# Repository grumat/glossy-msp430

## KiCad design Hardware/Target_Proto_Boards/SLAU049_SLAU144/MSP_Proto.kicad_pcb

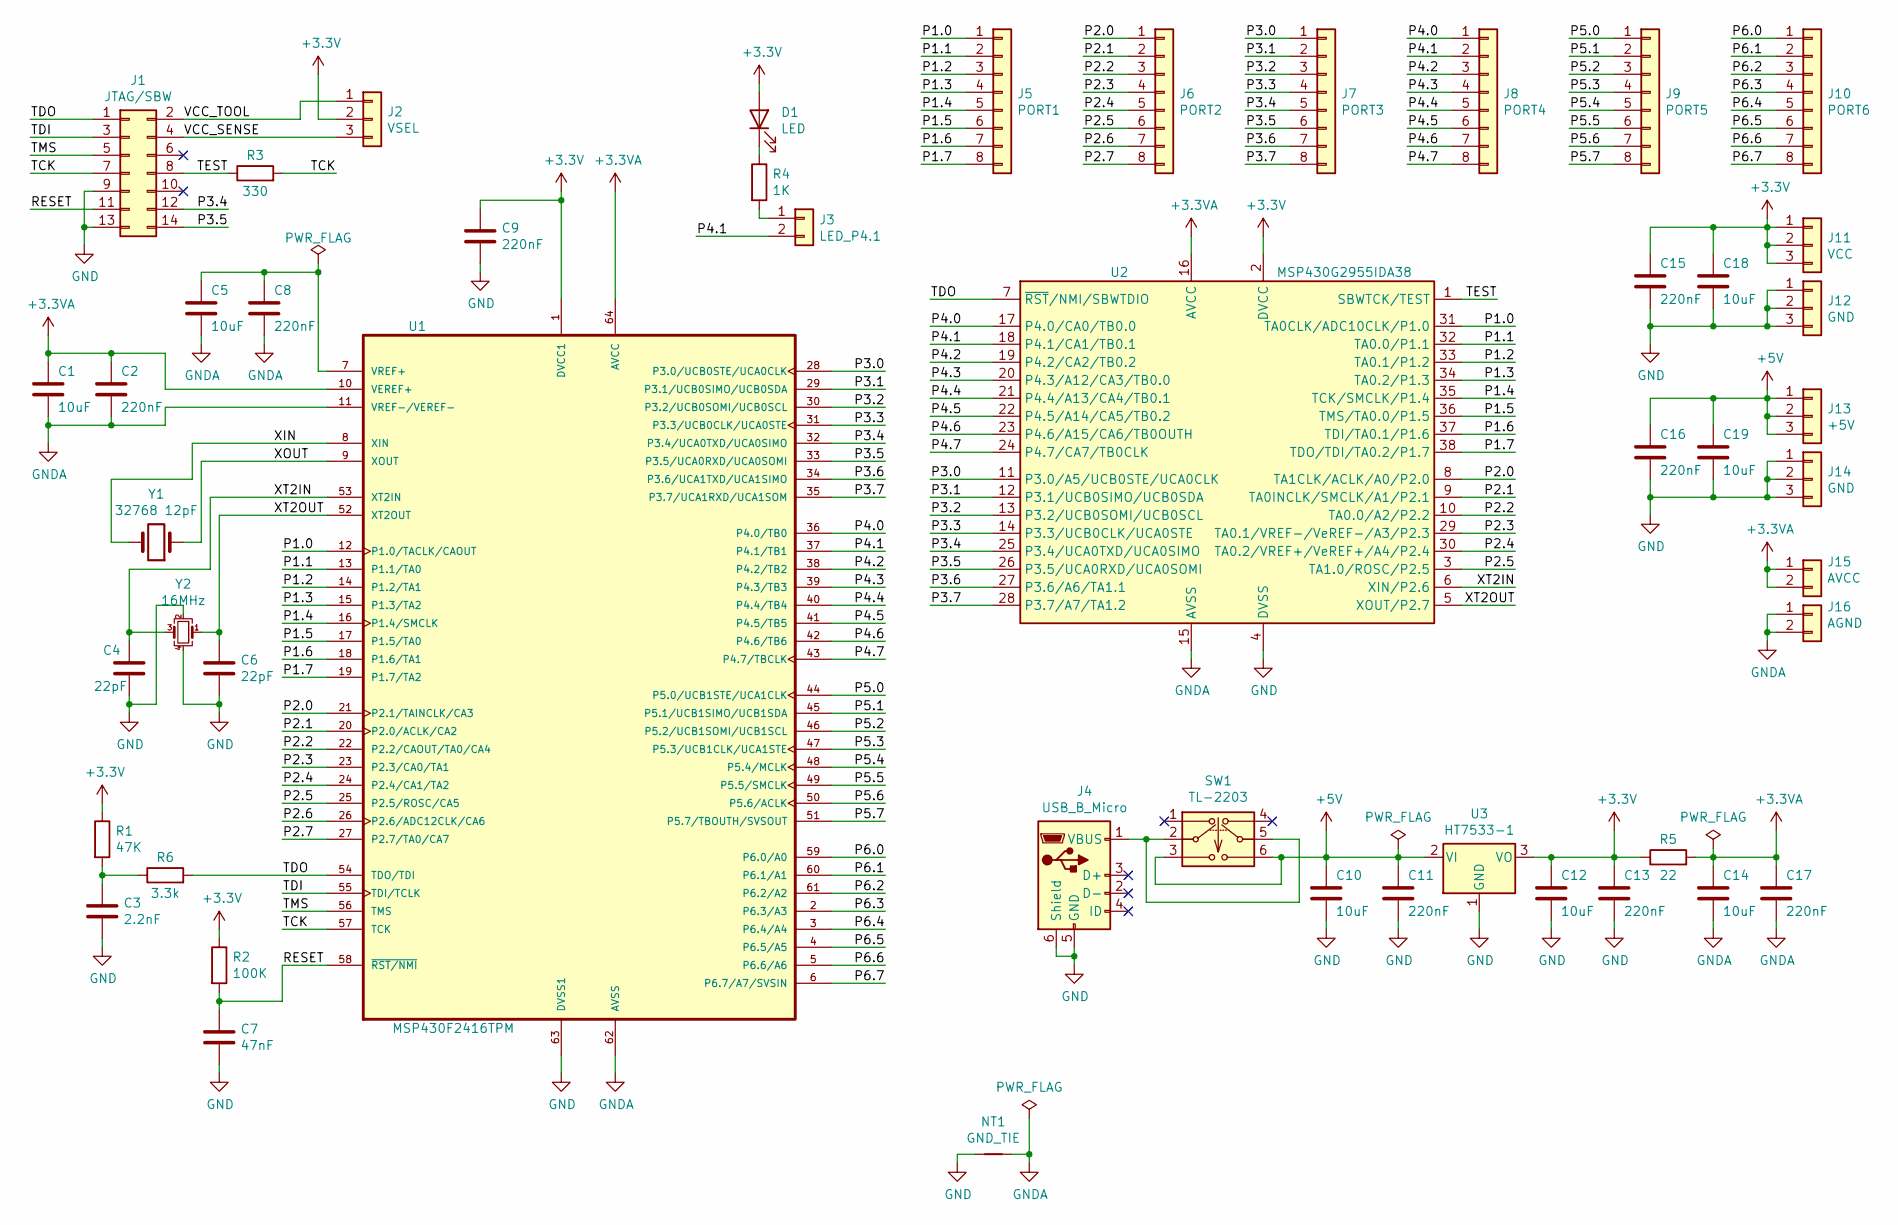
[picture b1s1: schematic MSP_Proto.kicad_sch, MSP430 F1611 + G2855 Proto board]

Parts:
C1, C5, C10, C12, C14, C18, C19: 10uF; C_0603_1608Metric_Pad1.08x0.95mm_HandSolder; LCSC C19702
C2, C8, C9, C11, C13, C15, C16, C17: 220nF; C_0603_1608Metric_Pad1.08x0.95mm_HandSolder; LCSC C21120
C3: 2.2nF; C_0603_1608Metric_Pad1.08x0.95mm_HandSolder; LCSC C1604
C4, C6: 22pF; C_0603_1608Metric_Pad1.08x0.95mm_HandSolder; LCSC C1653
C7: 47nF; C_0603_1608Metric_Pad1.08x0.95mm_HandSolder; LCSC C1622
D1: LED; LED_0603_1608Metric_Pad1.05x0.95mm_HandSolder; LCSC C72038
J1: JTAG/SBW; IDC-Header_2x07_P2.54mm_Vertical
J2: VSEL; PinHeader_1x03_P2.54mm_Vertical
J3: LED_P4.1; PinHeader_1x02_P2.54mm_Vertical
J4: USB_B_Micro; USB_Micro-B_Molex-105017-0001-handsolder; LCSC C10418
J5: PORT1; PinHeader_1x08_P2.54mm_Vertical
J6: PORT2; PinHeader_1x08_P2.54mm_Vertical
J7: PORT3; PinHeader_1x08_P2.54mm_Vertical
J8: PORT4; PinHeader_1x08_P2.54mm_Vertical
J9: PORT5; PinHeader_1x08_P2.54mm_Vertical
J10: PORT6; PinHeader_1x08_P2.54mm_Vertical
J11: VCC; PinHeader_1x03_P2.54mm_Vertical
J12, J14: GND; PinHeader_1x03_P2.54mm_Vertical
J13: +5V; PinHeader_1x03_P2.54mm_Vertical
J15: AVCC; PinHeader_1x02_P2.54mm_Vertical
J16: AGND; PinHeader_1x02_P2.54mm_Vertical
NT1: GND_TIE; NetTie-2_THT_Pad0.3mm
R1: 47K; R_0603_1608Metric_Pad0.98x0.95mm_HandSolder; LCSC C25819
R2: 100K; R_0603_1608Metric_Pad0.98x0.95mm_HandSolder; LCSC C25803
R3: 330; R_0603_1608Metric_Pad0.98x0.95mm_HandSolder; LCSC C23138
R4: 1K; R_0603_1608Metric_Pad0.98x0.95mm_HandSolder; LCSC C21190
R5: 22; R_0603_1608Metric_Pad0.98x0.95mm_HandSolder; LCSC C23345
R6: 3.3k; R_0603_1608Metric_Pad0.98x0.95mm_HandSolder; LCSC C22978
SW1: TL-2203
U1: MSP430F2416TPM; LQFP-64_10x10mm_P0.5mm
U2: MSP430G2955IDA38; TSSOP-38_6.1x12.5mm_P0.65mm
U3: HT7533-1; SOT-89-3_Handsoldering; LCSC C14289
Y1: 32768 12pF; Crystal_SMD_G8-2Pin_3.2x1.5mm_HandSoldering; LCSC C32346
Y2: 16MHz; Crystal_SMD_3225-4Pin_3.2x2.5mm_HandSoldering; LCSC C13738

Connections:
+3.3VA: C1.1, C2.1, C14.1, C17.1, J15.1, J15.2, R5.2, U1.10 (VEREF+), U1.64 (AVCC), U2.16 (AVCC)
+3V3: C9.1, C12.1, C13.1, C15.1, C18.1, D1.2 (A), J2.2, J11.1, J11.2, J11.3, R1.1, R2.1, R5.1, U1.1 (DVCC1), U2.2 (DVCC), U3.3 (VO)
+5V: C10.1, C11.1, C16.1, C19.1, J13.1, J13.2, J13.3, SW1.3, SW1.6, U3.2 (VI)
/P1.0: J5.1, U1.12 (P1.0/TACLK/CAOUT), U2.31 (TA0CLK/ADC10CLK/P1.0)
/P1.1: J5.2, U1.13 (P1.1/TA0), U2.32 (TA0.0/P1.1)
/P1.2: J5.3, U1.14 (P1.2/TA1), U2.33 (TA0.1/P1.2)
/P1.3: J5.4, U1.15 (P1.3/TA2), U2.34 (TA0.2/P1.3)
/P1.4: J5.5, U1.16 (P1.4/SMCLK), U2.35 (TCK/SMCLK/P1.4)
/P1.5: J5.6, U1.17 (P1.5/TA0), U2.36 (TMS/TA0.0/P1.5)
/P1.6: J5.7, U1.18 (P1.6/TA1), U2.37 (TDI/TA0.1/P1.6)
/P1.7: J5.8, U1.19 (P1.7/TA2), U2.38 (TDO/TDI/TA0.2/P1.7)
/P2.0: J6.1, U1.21 (P2.1/TAINCLK/CA3), U2.8 (TA1CLK/ACLK/A0/P2.0)
/P2.1: J6.2, U1.20 (P2.0/ACLK/CA2), U2.9 (TA0INCLK/SMCLK/A1/P2.1)
/P2.2: J6.3, U1.22 (P2.2/CAOUT/TA0/CA4), U2.10 (TA0.0/A2/P2.2)
/P2.3: J6.4, U1.23 (P2.3/CA0/TA1), U2.29 (TA0.1/VREF-/VeREF-/A3/P2.3)
/P2.4: J6.5, U1.24 (P2.4/CA1/TA2), U2.30 (TA0.2/VREF+/VeREF+/A4/P2.4)
/P2.5: J6.6, U1.25 (P2.5/ROSC/CA5), U2.3 (TA1.0/ROSC/P2.5)
/P2.6: J6.7, U1.26 (P2.6/ADC12CLK/CA6)
/P2.7: J6.8, U1.27 (P2.7/TA0/CA7)
/P3.0: J7.1, U1.28 (P3.0/UCB0STE/UCA0CLK), U2.11 (P3.0/A5/UCB0STE/UCA0CLK)
/P3.1: J7.2, U1.29 (P3.1/UCB0SIMO/UCB0SDA), U2.12 (P3.1/UCB0SIMO/UCB0SDA)
/P3.2: J7.3, U1.30 (P3.2/UCB0SOMI/UCB0SCL), U2.13 (P3.2/UCB0SOMI/UCB0SCL)
/P3.3: J7.4, U1.31 (P3.3/UCB0CLK/UCA0STE), U2.14 (P3.3/UCB0CLK/UCA0STE)
/P3.4: J1.12, J7.5, U1.32 (P3.4/UCA0TXD/UCA0SIMO), U2.25 (P3.4/UCA0TXD/UCA0SIMO)
/P3.5: J1.14, J7.6, U1.33 (P3.5/UCA0RXD/UCA0SOMI), U2.26 (P3.5/UCA0RXD/UCA0SOMI)
/P3.6: J7.7, U1.34 (P3.6/UCA1TXD/UCA1SIMO), U2.27 (P3.6/A6/TA1.1)
/P3.7: J7.8, U1.35 (P3.7/UCA1RXD/UCA1SOM), U2.28 (P3.7/A7/TA1.2)
/P4.0: J8.1, U1.36 (P4.0/TB0), U2.17 (P4.0/CA0/TB0.0)
/P4.1: J3.2, J8.2, U1.37 (P4.1/TB1), U2.18 (P4.1/CA1/TB0.1)
/P4.2: J8.3, U1.38 (P4.2/TB2), U2.19 (P4.2/CA2/TB0.2)
/P4.3: J8.4, U1.39 (P4.3/TB3), U2.20 (P4.3/A12/CA3/TB0.0)
/P4.4: J8.5, U1.40 (P4.4/TB4), U2.21 (P4.4/A13/CA4/TB0.1)
/P4.5: J8.6, U1.41 (P4.5/TB5), U2.22 (P4.5/A14/CA5/TB0.2)
/P4.6: J8.7, U1.42 (P4.6/TB6), U2.23 (P4.6/A15/CA6/TB0OUTH)
/P4.7: J8.8, U1.43 (P4.7/TBCLK), U2.24 (P4.7/CA7/TB0CLK)
/P5.0: J9.1, U1.44 (P5.0/UCB1STE/UCA1CLK)
/P5.1: J9.2, U1.45 (P5.1/UCB1SIMO/UCB1SDA)
/P5.2: J9.3, U1.46 (P5.2/UCB1SOMI/UCB1SCL)
/P5.3: J9.4, U1.47 (P5.3/UCB1CLK/UCA1STE)
/P5.4: J9.5, U1.48 (P5.4/MCLK)
/P5.5: J9.6, U1.49 (P5.5/SMCLK)
/P5.6: J9.7, U1.50 (P5.6/ACLK)
/P5.7: J9.8, U1.51 (P5.7/TBOUTH/SVSOUT)
/P6.0: J10.1, U1.59 (P6.0/A0)
/P6.1: J10.2, U1.60 (P6.1/A1)
/P6.2: J10.3, U1.61 (P6.2/A2)
/P6.3: J10.4, U1.2 (P6.3/A3)
/P6.4: J10.5, U1.3 (P6.4/A4)
/P6.5: J10.6, U1.4 (P6.5/A5)
/P6.6: J10.7, U1.5 (P6.6/A6)
/P6.7: J10.8, U1.6 (P6.7/A7/SVSIN)
/RESET: C7.1, J1.11, R2.2, U1.58 (~RST/NMI)
/TCK: J1.7, R3.2, U1.57 (TCK)
/TDI: J1.3, U1.55 (TDI/TCLK)
/TDO: J1.1, R6.2, U1.54 (TDO/TDI), U2.7 (~RST/NMI/SBWTDIO)
/TEST: J1.8, R3.1, U2.1 (SBWTCK/TEST)
/TMS: J1.5, U1.56 (TMS)
/VCC_SENSE: J1.4, J2.3
/VCC_TOOL: J1.2, J2.1
/XIN: U1.8 (XIN), Y1.2
/XOUT: U1.9 (XOUT), Y1.1
/XT2IN: C4.1, U1.53 (XT2IN), U2.6 (XIN/P2.6), Y2.3
/XT2OUT: C6.1, U1.52 (XT2OUT), U2.5 (XOUT/P2.7), Y2.1
GND: C3.2, C4.2, C6.2, C7.2, C9.2, C10.2, C11.2, C12.2, C13.2, C15.2, C16.2, C18.2, C19.2, J1.9, J1.13, J4.5 (GND), J4.6 (Shield), J12.1, J12.2, J12.3, J14.1, J14.2, J14.3, NT1.1, U1.63 (DVSS1), U2.4 (DVSS), U3.1 (GND), Y2.2, Y2.4
GNDA: C1.2, C2.2, C5.2, C8.2, C14.2, C17.2, J16.1, J16.2, NT1.2, U1.11 (VREF-/VEREF-), U1.62 (AVSS), U2.15 (AVSS)
unnamed: C3.1, R1.2, R6.1
unnamed: C5.1, C8.1, U1.7 (VREF+)
unnamed: D1.1 (K), R4.1
unnamed: J3.1, R4.2
unnamed: J4.1 (VBUS), SW1.2, SW1.5

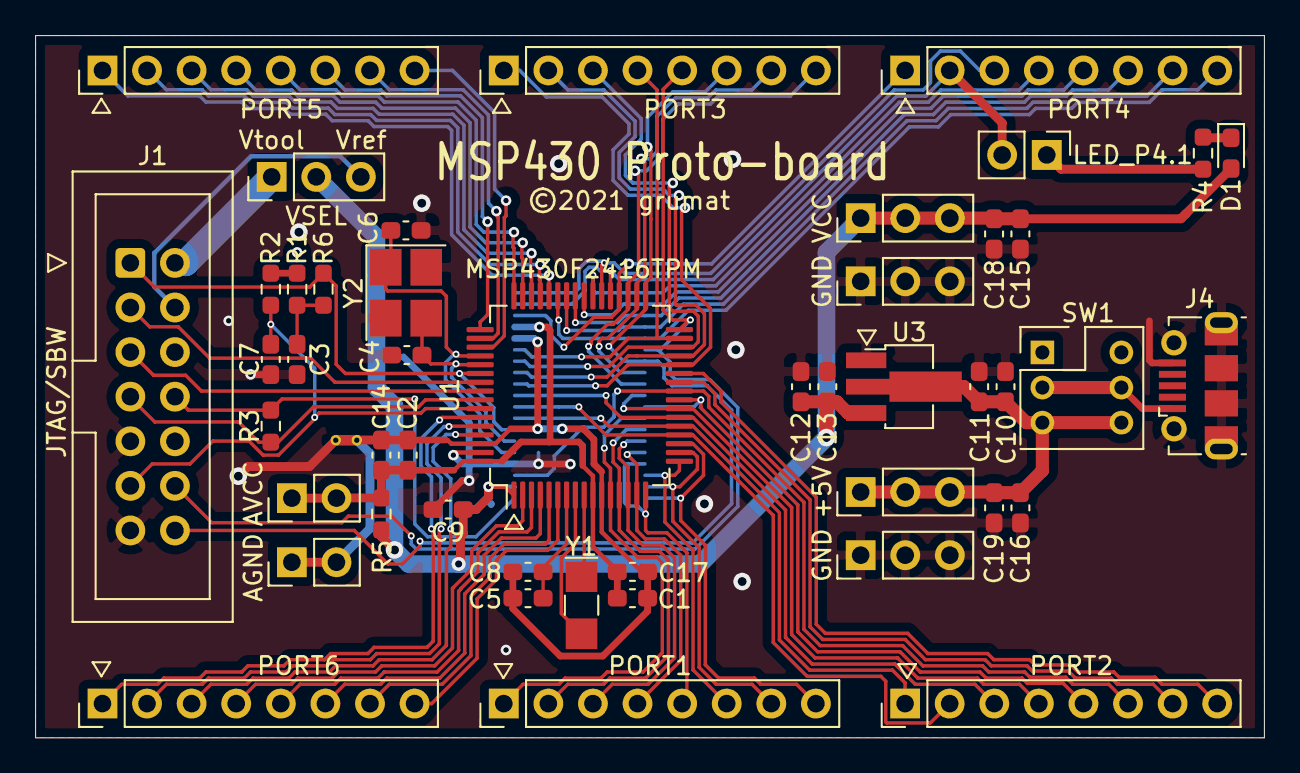
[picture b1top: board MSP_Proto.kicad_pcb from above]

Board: 2 copper layers, 70.0 x 40.0 mm, 49 parts (1 on the bottom side), 70 nets.

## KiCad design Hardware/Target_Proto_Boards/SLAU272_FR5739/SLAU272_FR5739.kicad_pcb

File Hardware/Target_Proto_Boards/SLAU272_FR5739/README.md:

# MSP430FR5739 Proto Board

> For testing devices of family **SLAU272**.

The proto-board for the MSP430FR5739 family is target for the newer FRAM 
devices with TSSOP-38. There are not so many options with this pin-out, 
but FRAM changes JTAG operations quite a lot, so it is worth the 
investment for the development of a embracing MSPBMP firmware.

This board offers many configuration options as these chips support JTAG 
and SBW and many reserved pins for legacy parts can now operate as GPIO. 
Then you have more jumpers and solder jumpers than on other prototype 
boards.

The pictures shows a 3D model of this prototype board:

These are the features:
- Support for a couple of TSSOP-38 FRAM parts: the MSP430FR5730, 
MSP430FR5731, MSP430FR5732, MSP430FR5733, MSP430FR5734, MSP430FR5735, 
MSP430FR5736, MSP430FR5737, MSP430FR5738 and MSP430FR5739.
- Standard 14-pin JTAG connector
- Configurable support for JTAG and Spi By Wire. SBW can be configured 
for standard TI emulators and Olimex MSP430-JTAG-Tiny-V2 emulators.
- Serial port on the JTAG connector.
- Support for power supply from JTAG connector or internal 3.3V regulator 
using a Micro USB cable.
- Configurable use of a 16 MHz crystal.
- Reset button.
- Configurable use of analog voltage (ADC support).
- Test led on P4.1 configurable by jumper.
- Al IO ports wired to accessible header pins.
- Header pins for VCC, USB +5V and GND.

## Top PCB view

## Bottom PCB view

# Users Guide

The following points describes general use of these boards.

## External USB power supply

To use the external power supply connect a powered µUSB cable into 
**J4**. For this case the switch **SW1** will control the power.

Before connecting a JTAG cable into **J12**, ensure that the **VSEL** 
jumper shorts the **Vref** position.

## Powering from the JTAG tool

During most simple tests with the board the best option is to power it 
from the JTAG emulator.

For this option just connect the JTAG tool to the **J12** JTAG connector 
and move the jumper on **VSEL** to the **Vtool** position. When the JTAG 
is connected and running it will supply the board with its internal power 
supply.

Note that the switch **SW1** and the **+5V** jumper has no effect on this 
configuration.

## Selecting JTAG or SBW Modes

Since pin-outs may differ for different debug emulators the board offers 
three different options in the **J5** jumper.

The silk screen indicates three jumpers that needs to be shorted for the 
standard JTAG interface. Actually JTAG requires a fourth jumper, which is 
the last one, shared with Olimex marking.

If you choose Spy-By-Wire, then you have two options: The silk-screen at 
the center indicates two jumpers for the standard TI connection or two 
jumpers for the Olimex MSP430-JTAG-Tiny-V2 emulators.

> These options are mutually exclusive: **do not connect multiple options 
> at the same time**.

### JTAG Configuration

For the JTAG mode the four jumpers connects the following pins:
- TDO --> TDO (P1.7)
- TCK --> TCK (P1.4)
- RST --> RESET
- TEST --> TEST

### Spy-By-Wire Configuration - TI pin-out

TI SBW uses the following connections:
- TDO --> RESET
- TCK --> TEST

> The MSPBMP device uses the TI pin layout.

### Spy-By-Wire Configuration - Olimex pin-out

Olimex SBW uses the following connections:
- RST --> RESET
- TEST --> TEST

## Reset Button

The Reset button can be used to restart the device. It is not 
advised to interrupt a running JTAG connection by pressing 
this button. Some references states that MCU may enter an 
undefined state.

## Attaching the Crystal

The crystal is by default not connected, since pins may be configured as 
a general GPIO port. To enable this function, short both solder bridges 
marked with the **XTAL** label.

## Analog Power Supply

The Analog supply pins are configurable as GPIO pins. To enable them as 
power source short both solder jumpers **AVCC** and **AGND**. In this 
case ensure not to set the pins with the GPIO function.

## Other Voltage Supplies

The board exposes all power supplies through jumpers. It is advised to 
follow good practice rules, as there are no kind of protection. The +5V 
pins are connected to a USB bus or power adapter. Low quality power 
sources may be a cause of issues.

## Using the LED function

To use the LED, just connect the **LED_P4.1** jumper.

A test program for the LED test could be:

```cpp
#include <msp430.h>

void Delay()
{
	long counter = 0;
	while (counter++ < 5000)
		asm("nop");
}

void MainLoop()
{
	WDTCTL = WDTPW | WDTHOLD;
	
	P4DIR |= (1 << 1);
	
	for (;;)
	{
		P4OUT |= (1 << 1);
		Delay();
		P4OUT &= ~(1 << 1);
		Delay();
	}
}

int main()
{
	MainLoop();
}
```

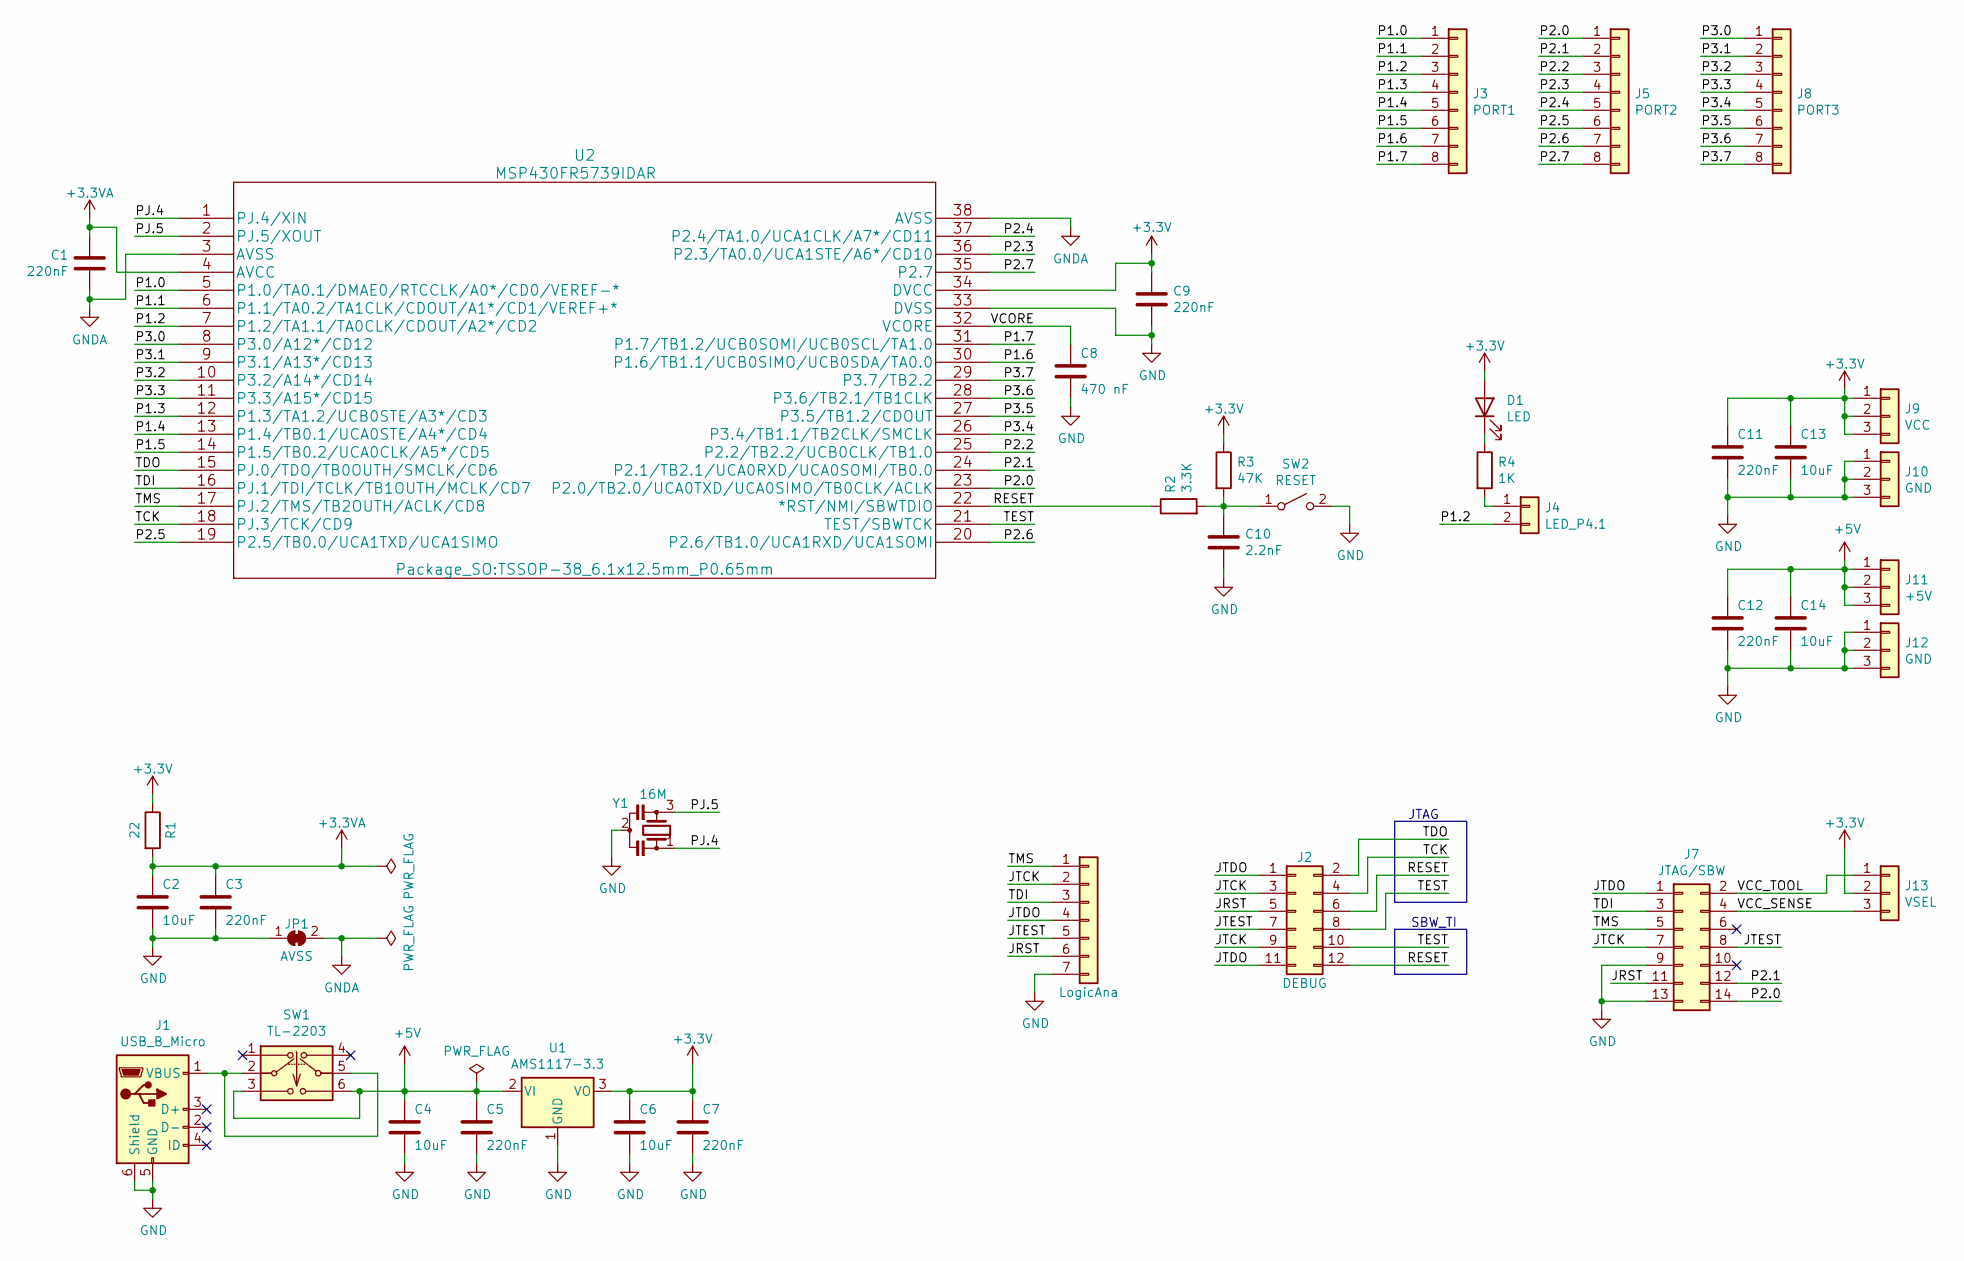
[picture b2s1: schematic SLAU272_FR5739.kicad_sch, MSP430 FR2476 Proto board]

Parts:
C1, C3, C5, C7, C9, C11, C12: 220nF; C_0603_1608Metric_Pad1.08x0.95mm_HandSolder; LCSC C21120
C2, C4, C6, C13, C14: 10uF; C_0603_1608Metric_Pad1.08x0.95mm_HandSolder; LCSC C19702
C8: 470 nF; C_0603_1608Metric_Pad1.08x0.95mm_HandSolder; LCSC C15849
C10: 2.2nF; C_0603_1608Metric_Pad1.08x0.95mm_HandSolder; LCSC C1604
D1: LED; LED_0603_1608Metric_Pad1.05x0.95mm_HandSolder; LCSC C72038
J1: USB_B_Micro; USB_Micro-B_Molex-105017-0001-handsolder; LCSC C10418
J2: DEBUG; PinHeader_2x06_P2.54mm_Vertical
J3: PORT1; PinHeader_1x08_P2.54mm_Vertical
J4: LED_P4.1; PinHeader_1x02_P2.54mm_Vertical
J5: PORT2; PinHeader_1x08_P2.54mm_Vertical
J6: LogicAna; PinHeader_1x07_P2.54mm_Vertical
J7: JTAG/SBW; IDC-Header_2x07_P2.54mm_Vertical
J8: PORT3; PinHeader_1x08_P2.54mm_Vertical
J9: VCC; PinHeader_1x03_P2.54mm_Vertical
J10, J12: GND; PinHeader_1x03_P2.54mm_Vertical
J11: +5V; PinHeader_1x03_P2.54mm_Vertical
J13: VSEL; PinHeader_1x03_P2.54mm_Vertical
JP1: AVSS; SolderJumper-2_P1.3mm_Bridged_RoundedPad1.0x1.5mm
R1: 22; R_0603_1608Metric_Pad0.98x0.95mm_HandSolder; LCSC C23345
R2: 3.3K; R_0603_1608Metric_Pad0.98x0.95mm_HandSolder; LCSC C22978
R3: 47K; R_0603_1608Metric_Pad0.98x0.95mm_HandSolder
R4: 1K; R_0603_1608Metric_Pad0.98x0.95mm_HandSolder; LCSC C21190
SW1: TL-2203
SW2: RESET; SW_Push_SPST_NO_Alps_SKRK_handsolder; LCSC C720477
U1: AMS1117-3.3; SOT-89-3_Handsoldering; LCSC C14289
U2: MSP430FR5739IDAR; TSSOP-38_6.1x12.5mm_P0.65mm
Y1: 16M; Resonator_SMD_Murata_CSTxExxV-3Pin_3.0x1.1mm_HandSoldering

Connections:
+3.3V: C6.1, C7.1, C9.1, C11.1, C13.1, D1.2 (A), J9.1, J9.2, J9.3, J13.2, R1.1, R3.1, U1.3 (VO), U2.34 (DVCC)
+3.3VA: C1.1, C2.1, C3.1, R1.2, U2.4 (AVCC)
+5V: C4.1, C5.1, C12.1, C14.1, J11.1, J11.2, J11.3, SW1.3, SW1.6, U1.2 (VI)
/JRST: J2.5, J6.6, J7.11
/JTCK: J2.3, J2.9, J6.2, J7.7
/JTDO: J2.1, J2.11, J6.4, J7.1
/JTEST: J2.7, J6.5, J7.8
/P1.0: J3.1, U2.5 (P1.0/TA0.1/DMAE0/RTCCLK/A0*/CD0/VEREF-*)
/P1.1: J3.2, U2.6 (P1.1/TA0.2/TA1CLK/CDOUT/A1*/CD1/VEREF+*)
/P1.2: J3.3, J4.2, U2.7 (P1.2/TA1.1/TA0CLK/CDOUT/A2*/CD2)
/P1.3: J3.4, U2.12 (P1.3/TA1.2/UCB0STE/A3*/CD3)
/P1.4: J3.5, U2.13 (P1.4/TB0.1/UCA0STE/A4*/CD4)
/P1.5: J3.6, U2.14 (P1.5/TB0.2/UCA0CLK/A5*/CD5)
/P1.6: J3.7, U2.30 (P1.6/TB1.1/UCB0SIMO/UCB0SDA/TA0.0)
/P1.7: J3.8, U2.31 (P1.7/TB1.2/UCB0SOMI/UCB0SCL/TA1.0)
/P2.0: J5.1, J7.14, U2.23 (P2.0/TB2.0/UCA0TXD/UCA0SIMO/TB0CLK/ACLK)
/P2.1: J5.2, J7.12, U2.24 (P2.1/TB2.1/UCA0RXD/UCA0SOMI/TB0.0)
/P2.2: J5.3, U2.25 (P2.2/TB2.2/UCB0CLK/TB1.0)
/P2.3: J5.4, U2.36 (P2.3/TA0.0/UCA1STE/A6*/CD10)
/P2.4: J5.5, U2.37 (P2.4/TA1.0/UCA1CLK/A7*/CD11)
/P2.5: J5.6, U2.19 (P2.5/TB0.0/UCA1TXD/UCA1SIMO)
/P2.6: J5.7, U2.20 (P2.6/TB1.0/UCA1RXD/UCA1SOMI)
/P2.7: J5.8, U2.35 (P2.7)
/P3.0: J8.1, U2.8 (P3.0/A12*/CD12)
/P3.1: J8.2, U2.9 (P3.1/A13*/CD13)
/P3.2: J8.3, U2.10 (P3.2/A14*/CD14)
/P3.3: J8.4, U2.11 (P3.3/A15*/CD15)
/P3.4: J8.5, U2.26 (P3.4/TB1.1/TB2CLK/SMCLK)
/P3.5: J8.6, U2.27 (P3.5/TB1.2/CDOUT)
/P3.6: J8.7, U2.28 (P3.6/TB2.1/TB1CLK)
/P3.7: J8.8, U2.29 (P3.7/TB2.2)
/PJ.4: U2.1 (PJ.4/XIN), Y1.1
/PJ.5: U2.2 (PJ.5/XOUT), Y1.3
/RESET: J2.6, J2.12, R2.1, U2.22 (*RST/NMI/SBWTDIO)
/TCK: J2.4, U2.18 (PJ.3/TCK/CD9)
/TDI: J6.3, J7.3, U2.16 (PJ.1/TDI/TCLK/TB1OUTH/MCLK/CD7)
/TDO: J2.2, U2.15 (PJ.0/TDO/TB0OUTH/SMCLK/CD6)
/TEST: J2.8, J2.10, U2.21 (TEST/SBWTCK)
/TMS: J6.1, J7.5, U2.17 (PJ.2/TMS/TB2OUTH/ACLK/CD8)
/VCC_SENSE: J7.4, J13.3
/VCC_TOOL: J7.2, J13.1
/VCORE: C8.1, U2.32 (VCORE)
GND: C2.2, C3.2, C4.2, C5.2, C6.2, C7.2, C8.2, C9.2, C10.2, C11.2, C12.2, C13.2, C14.2, J1.5 (GND), J1.6 (Shield), J6.7, J7.9, J7.13, J10.1, J10.2, J10.3, J12.1, J12.2, J12.3, JP1.1 (A), SW2.2 (B), U1.1 (GND), U2.33 (DVSS), Y1.2
GNDA: C1.2, JP1.2 (B), U2.3 (AVSS), U2.38 (AVSS)
unnamed: C10.1, R2.2, R3.2, SW2.1 (A)
unnamed: D1.1 (K), R4.1
unnamed: J1.1 (VBUS), SW1.2, SW1.5
unnamed: J4.1, R4.2

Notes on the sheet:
SBW_TI
JTAG

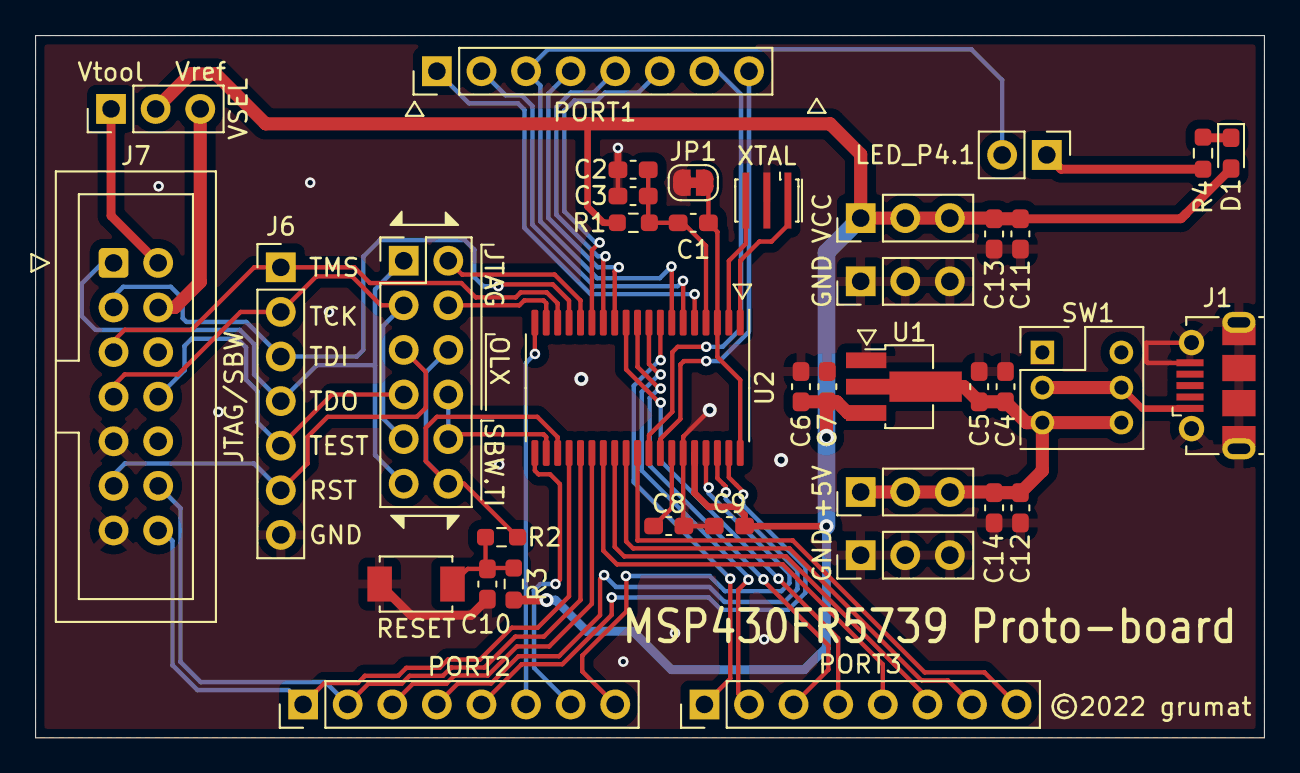
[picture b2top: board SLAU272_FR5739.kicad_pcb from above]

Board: 2 copper layers, 70.0 x 40.0 mm, 38 parts (0 on the bottom side), 48 nets.

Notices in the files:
Hardware/Target_Proto_Boards/SLAU049_SLAU144/MSP_Proto.kicad_pcb:
©2021 grumat
Hardware/Target_Proto_Boards/SLAU272_FR5739/SLAU272_FR5739.kicad_pcb:
©2022 grumat
